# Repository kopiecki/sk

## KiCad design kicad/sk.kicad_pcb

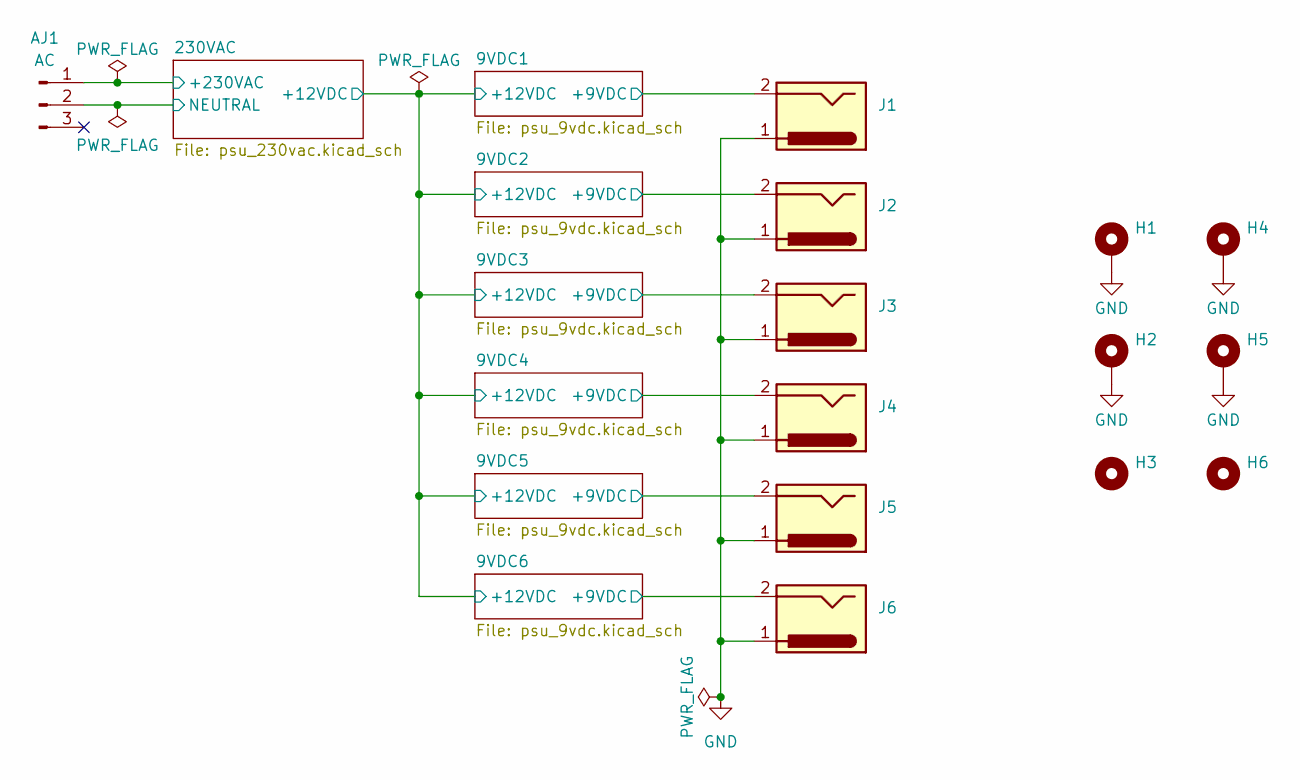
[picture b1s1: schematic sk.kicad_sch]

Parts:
AJ1: AC; 5430373
H1, H2, H4, H5: MountingHole_Pad; MountingHole_2.2mm_M2_ISO14580_Pad
H3, H6: MountingHole; MountingHole_2mm
J1, J2, J3, J4, J5, J6: Barrel_Jack; PJ002A

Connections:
/9VDC1/+9VDC: J1.2; also elsewhere on the board
/9VDC2/+9VDC: J2.2; also elsewhere on the board
/9VDC3/+9VDC: J3.2; also elsewhere on the board
/9VDC4/+9VDC: J4.2; also elsewhere on the board
/9VDC5/+9VDC: J5.2; also elsewhere on the board
/9VDC6/+9VDC: J6.2; also elsewhere on the board
/230VAC/+230VAC: AJ1.1; also elsewhere on the board
/230VAC/NEUTRAL: AJ1.2; also elsewhere on the board
GND: H1.1, H2.1, H4.1, H5.1, J1.1, J2.1, J3.1, J4.1, J5.1, J6.1; also elsewhere on the board

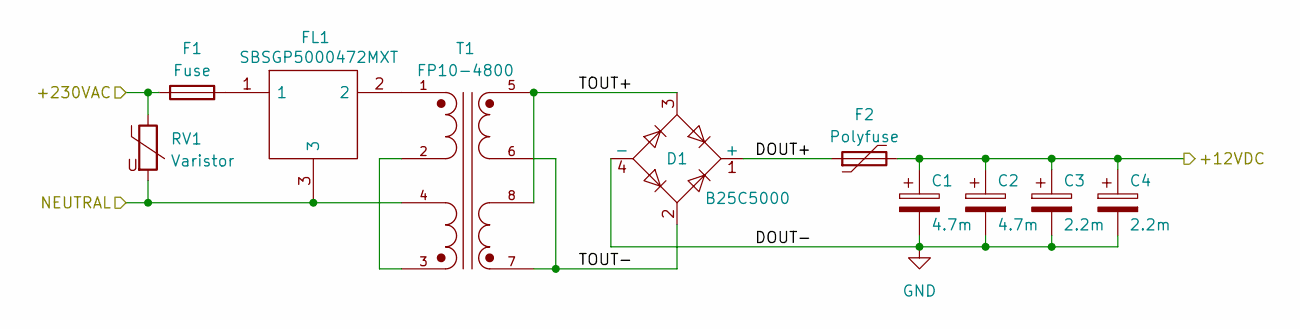
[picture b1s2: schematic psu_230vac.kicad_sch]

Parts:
C1, C2: 4.7m; CAPPRD1000W80D2200H3700
C3, C4: 2.2m; CAPPRD750W80D1600H3800
D1: B25C5000; Diode_Bridge_Vishay_GBU
F1: Fuse; FUSC6125X279N
F2: Polyfuse; FUSC7451X180N
FL1: SBSGP5000472MXT; Manufacturer_Part_Number SBSGP5000472MXT
RV1: Varistor; VARC8250X200N
T1: FP10-4800; XFMR_FP10-4800

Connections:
/230VAC/+12VDC: C1.1, C2.1, C3.1, C4.1, F2.2; also elsewhere on the board
/230VAC/+230VAC: F1.1, RV1.1; also elsewhere on the board
/230VAC/DOUT+: D1.1 (+), F2.1
/230VAC/NEUTRAL: FL1.3, RV1.2, T1.4; also elsewhere on the board
/230VAC/TOUT+: D1.3, T1.5, T1.8
/230VAC/TOUT-: D1.2, T1.6, T1.7
GND: C1.2, C2.2, C3.2, C4.2, D1.4 (-); also elsewhere on the board
unnamed: F1.2, FL1.1
unnamed: FL1.2, T1.1
unnamed: T1.2, T1.3

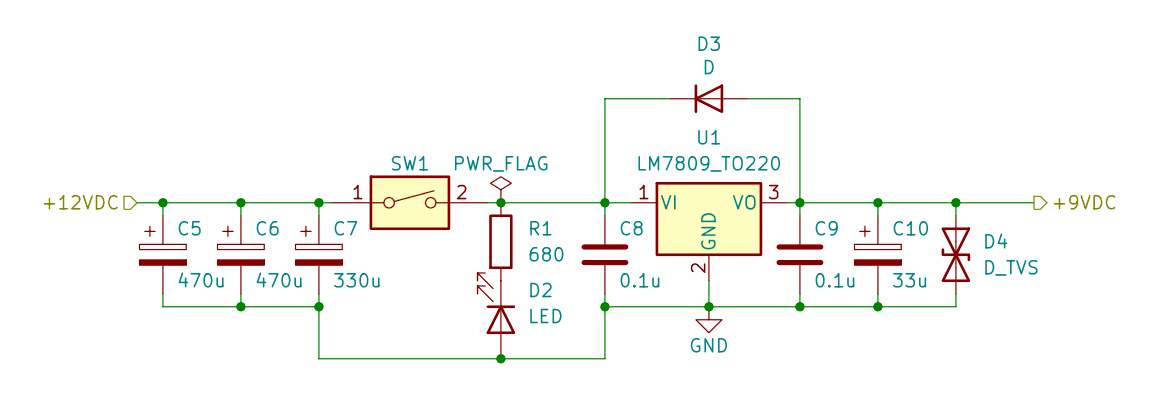
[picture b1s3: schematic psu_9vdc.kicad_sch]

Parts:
C5, C6: 470u; ESH_13X20_
C7: 330u; CAPPRD500W60D1000H2200
C8, C9: 0.1u; C_0805_2012Metric
C10: 33u; EEE0JA152UAP
D2: LED; D_0805_2012Metric
D3: D; SE8D20DHM3H
D4: D_TVS; D_SOD-523
R1: 680; R_0805_2012Metric
SW1: SW_DIP_x01; 200MSP1T1B1M2QEH
U1: LM7809_TO220; TO-220-3_Vertical

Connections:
/9VDC1/+9VDC: C9.1, C10.1, D3.2 (A), D4.1 (A1), U1.3 (VO); also elsewhere on the board
/230VAC/+12VDC: C5.1, C6.1, C7.1, SW1.1; also elsewhere on the board
GND: C5.2, C6.2, C7.2, C8.2, C9.2, C10.2, D2.2 (A), D4.2 (A2), U1.2 (GND); also elsewhere on the board
unnamed: D2.1 (K), R1.2
unnamed: C8.1, D3.1 (K), R1.1, SW1.2, U1.1 (VI)

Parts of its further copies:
C11, C12, C17, C18, C23, C24, C29, C30, C35, C36: 470u; ESH_13X20_
C13, C19, C25, C31, C37: 330u; CAPPRD500W60D1000H2200
C14, C15, C20, C21, C26, C27, C32, C33, C38, C39: 0.1u; C_0805_2012Metric
C16, C22, C28, C34, C40: 33u; EEE0JA152UAP
D5, D8, D11, D14, D17: LED; D_0805_2012Metric
D6, D9, D12, D15, D18: D; SE8D20DHM3H
D7, D10, D13, D16, D19: D_TVS; D_SOD-523
R2, R3, R4, R5, R6: 680; R_0805_2012Metric
SW2, SW3, SW4, SW5, SW6: SW_DIP_x01; 200MSP1T1B1M2QEH
U2, U3, U4, U5, U6: LM7809_TO220; TO-220-3_Vertical

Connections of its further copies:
/9VDC2/+9VDC: C15.1, C16.1, D6.2 (A), D7.1 (A1), U2.3 (VO); also elsewhere on the board
/9VDC3/+9VDC: C21.1, C22.1, D9.2 (A), D10.1 (A1), U3.3 (VO); also elsewhere on the board
/9VDC4/+9VDC: C27.1, C28.1, D12.2 (A), D13.1 (A1), U4.3 (VO); also elsewhere on the board
/9VDC5/+9VDC: C33.1, C34.1, D15.2 (A), D16.1 (A1), U5.3 (VO); also elsewhere on the board
/9VDC6/+9VDC: C39.1, C40.1, D18.2 (A), D19.1 (A1), U6.3 (VO); also elsewhere on the board
/230VAC/+12VDC: C11.1, C12.1, C13.1, C17.1, C18.1, C19.1, C23.1, C24.1, C25.1, C29.1, C30.1, C31.1, C35.1, C36.1, C37.1, SW2.1, SW3.1, SW4.1, SW5.1, SW6.1; also elsewhere on the board
GND: C11.2, C12.2, C13.2, C14.2, C15.2, C16.2, C17.2, C18.2, C19.2, C20.2, C21.2, C22.2, C23.2, C24.2, C25.2, C26.2, C27.2, C28.2, C29.2, C30.2, C31.2, C32.2, C33.2, C34.2, C35.2, C36.2, C37.2, C38.2, C39.2, C40.2, D5.2 (A), D7.2 (A2), D8.2 (A), D10.2 (A2), D11.2 (A), D13.2 (A2), D14.2 (A), D16.2 (A2), D17.2 (A), D19.2 (A2), U2.2 (GND), U3.2 (GND), U4.2 (GND), U5.2 (GND), U6.2 (GND); also elsewhere on the board
unnamed: D5.1 (K), R2.2
unnamed: C14.1, D6.1 (K), R2.1, SW2.2, U2.1 (VI)
unnamed: D8.1 (K), R3.2
unnamed: C20.1, D9.1 (K), R3.1, SW3.2, U3.1 (VI)
unnamed: D11.1 (K), R4.2
unnamed: C26.1, D12.1 (K), R4.1, SW4.2, U4.1 (VI)
unnamed: D14.1 (K), R5.2
unnamed: C32.1, D15.1 (K), R5.1, SW5.2, U5.1 (VI)
unnamed: D17.1 (K), R6.2
unnamed: C38.1, D18.1 (K), R6.1, SW6.2, U6.1 (VI)

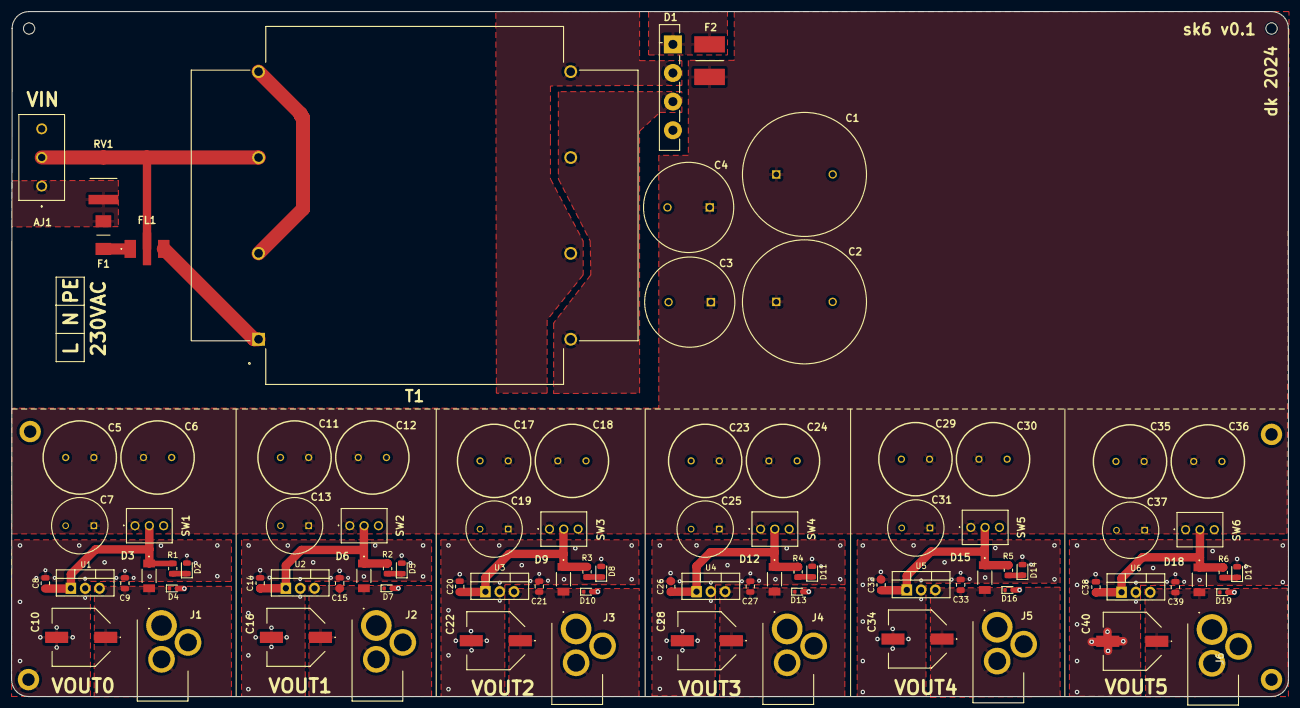
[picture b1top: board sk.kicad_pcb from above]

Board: 2 copper layers, 226.5 x 121.5 mm, 95 parts (0 on the bottom side), 28 nets.

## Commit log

2024-03-10 add kicad files
2024-03-15 Cleanup later
2024-03-15 Post zip cleanups
2024-03-17 Initial PCB layout
2024-03-18 Add more PCB routings
2024-03-19 Make PCB rework
2024-03-20 Enhance PCB
2024-03-21 Post review
